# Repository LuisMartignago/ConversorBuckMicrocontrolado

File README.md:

# Conversor Buck Microcontrolado

Projeto de um conversor CC-CC abaixador (Buck Converter) com controle digital implementado em um microcontrolador **CH32V003**, desenvolvido com foco em aplicações de eletrônica de potência, sistemas embarcados e controle digital.

O projeto contempla o desenvolvimento completo do hardware e do firmware, incluindo o dimensionamento da etapa de potência, condicionamento dos sinais analógicos, controle por PWM, algoritmo de controle PI, proteção contra sobrecorrente e interface de comunicação serial.

---

## Principais características

* Conversor Buck microcontrolado.
* Controle digital de tensão utilizando controlador **PI**.
* Geração de PWM por hardware utilizando o temporizador **TIM1**.
* Aquisição de tensão e corrente através do ADC.
* Conversão automática utilizando **ADC + DMA**.
* Comunicação serial UART para monitoramento e configuração.
* Limitação de corrente por software.
* Controle de rampa (*Rate Limiter*) para partida suave e alterações da referência.
* Proteção contra *Integral Windup*.
* Firmware desenvolvido em linguagem C.
* Hardware desenvolvido no KiCad.

---

## Hardware

O conversor é composto pelos seguintes blocos principais:

* Microcontrolador **CH32V003**;
* Conversor Buck de potência;
* Driver para acionamento do MOSFET;
* Fonte auxiliar isolada para alimentação do gate driver;
* Reguladores de tensão para alimentação dos circuitos de controle;
* Divisor resistivo para medição da tensão;
* Resistor shunt para medição da corrente;
* Amplificador operacional interno do CH32V003 para condicionamento do sinal de corrente.

---

## Estratégia de controle

O controle da tensão de saída é realizado por um controlador **Proporcional–Integral (PI)**.

A implementação inclui:

* cálculo periódico do erro;
* atualização do termo integral;
* limitação do integrador (*Anti-Windup*);
* saturação da saída do controlador;
* atualização do ciclo de trabalho do PWM.

Para reduzir transitórios durante alterações da referência, foi implementado um algoritmo de **Rate Limiter**, permitindo variações graduais da tensão de saída.

Como mecanismo adicional de proteção, quando a corrente ultrapassa o limite configurado, a referência de tensão é reduzida gradualmente e o integrador do controlador é parcialmente descarregado, proporcionando recuperação rápida após a remoção da condição de sobrecorrente.

---

## Comunicação Serial

O firmware disponibiliza uma interface UART para:

* monitoramento da tensão;
* monitoramento da corrente;
* ajuste de parâmetros;
* depuração do sistema.

A transmissão utiliza **DMA**, reduzindo significativamente a utilização da CPU.

---

## Estrutura do repositório

```text
.
├── Firmware/
├── Hardware/
│   ├── Esquemáticos
│   ├── PCB
│   └── Bibliotecas
├── Documentação/
├── Imagens/
└── README.md
```

---

## Ferramentas utilizadas

* KiCad
* GCC para RISC-V
* WCH MounRiver Studio
* Git
* GitHub

---

## Aplicações

Este projeto pode ser utilizado como base para:

* estudos de Eletrônica de Potência;
* Sistemas Embarcados;
* Controle Digital;
* Fontes chaveadas;
* Conversores CC-CC;
* projetos acadêmicos;
* trabalhos de conclusão de curso.

---

## Licença

Este projeto está disponibilizado para fins acadêmicos e de pesquisa.

---

Caso este projeto seja utilizado em trabalhos acadêmicos, solicita-se a devida citação do repositório.

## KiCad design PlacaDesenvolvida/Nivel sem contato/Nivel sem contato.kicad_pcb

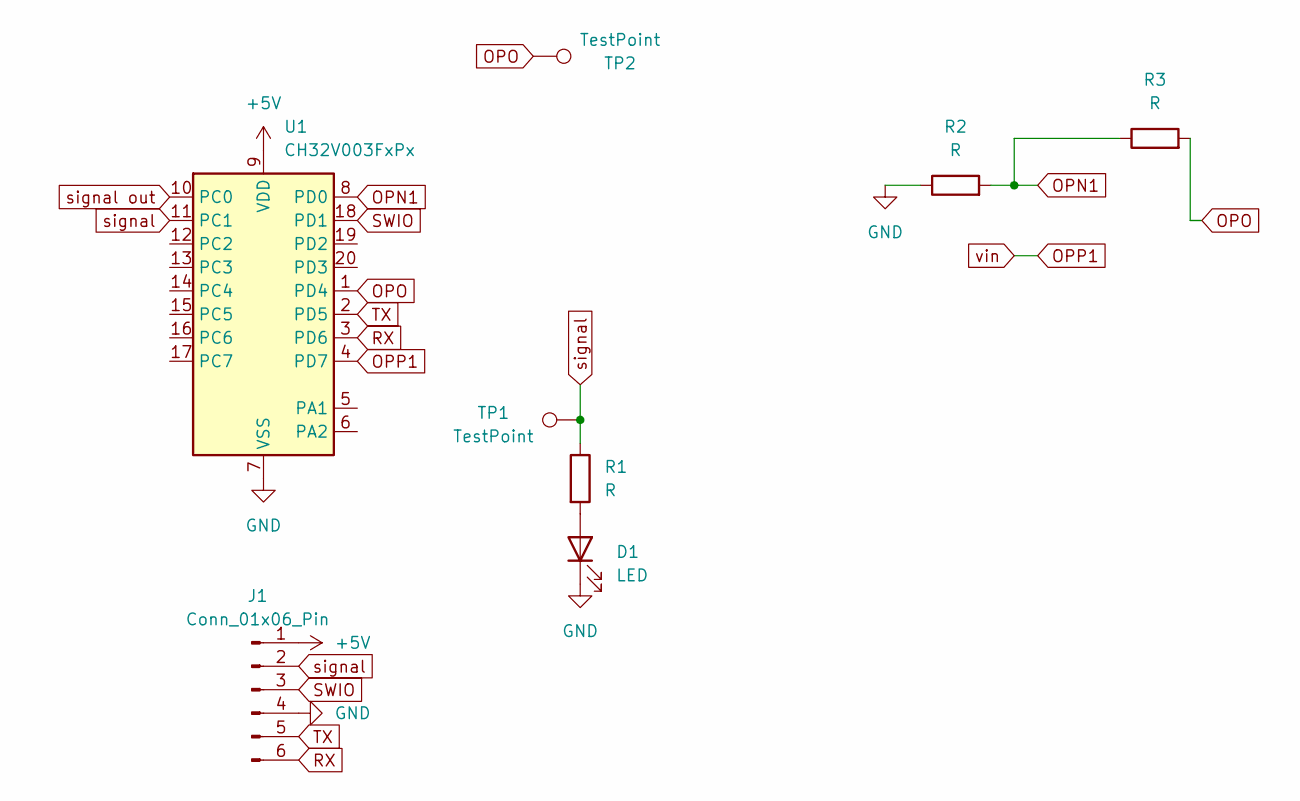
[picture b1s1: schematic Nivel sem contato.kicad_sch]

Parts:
D1: LED; LED_0805_2012Metric
J1: Conn_01x06_Pin; PinHeader_1x06_P2.54mm_Vertical
R1, R2, R3: R; R_0805_2012Metric
TP1, TP2: TestPoint; TestPoint_Bridge_Pitch2.54mm_Drill0.7mm
U1: CH32V003FxPx; TSSOP-20_4.4x6.5mm_P0.65mm

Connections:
+5V: J1.1, U1.9 (VDD)
GND: D1.1 (K), J1.4, R2.1, U1.7 (VSS)
unnamed: D1.2 (A), R1.2
OPN1: R2.2, R3.1, U1.8 (PD0)
OPO: R3.2, TP2.1 (1_1), U1.1 (PD4)
OPP1: U1.4 (PD7)
RX: J1.6, U1.3 (PD6)
SWIO: J1.3, U1.18 (PD1)
TX: J1.5, U1.2 (PD5)
signal: J1.2, R1.1, TP1.1 (1_1), U1.11 (PC1)
signal out: U1.10 (PC0)

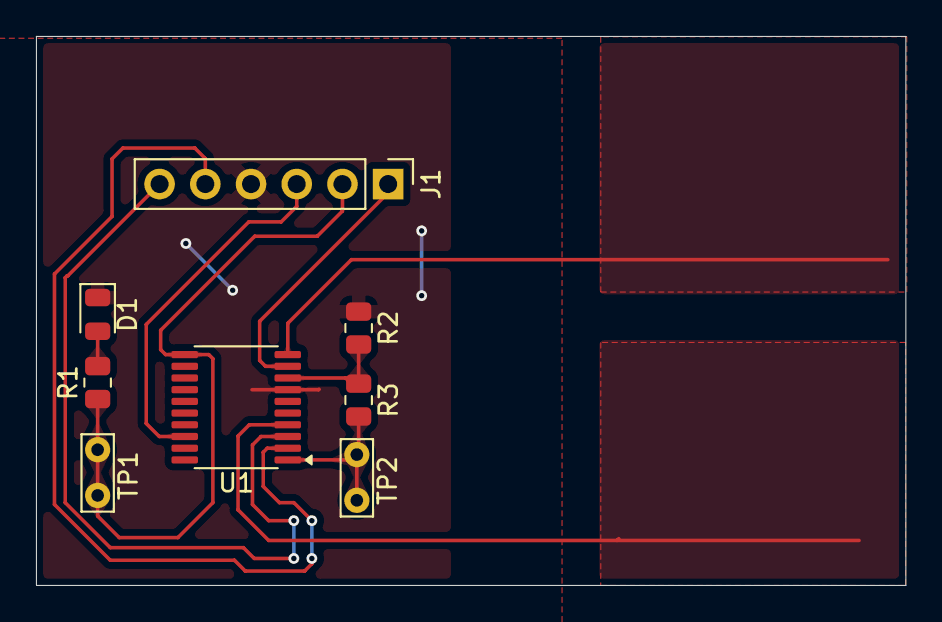
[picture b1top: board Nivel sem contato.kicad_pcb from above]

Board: 2 copper layers, 48.3 x 30.5 mm, 8 parts (0 on the bottom side), 9 nets.

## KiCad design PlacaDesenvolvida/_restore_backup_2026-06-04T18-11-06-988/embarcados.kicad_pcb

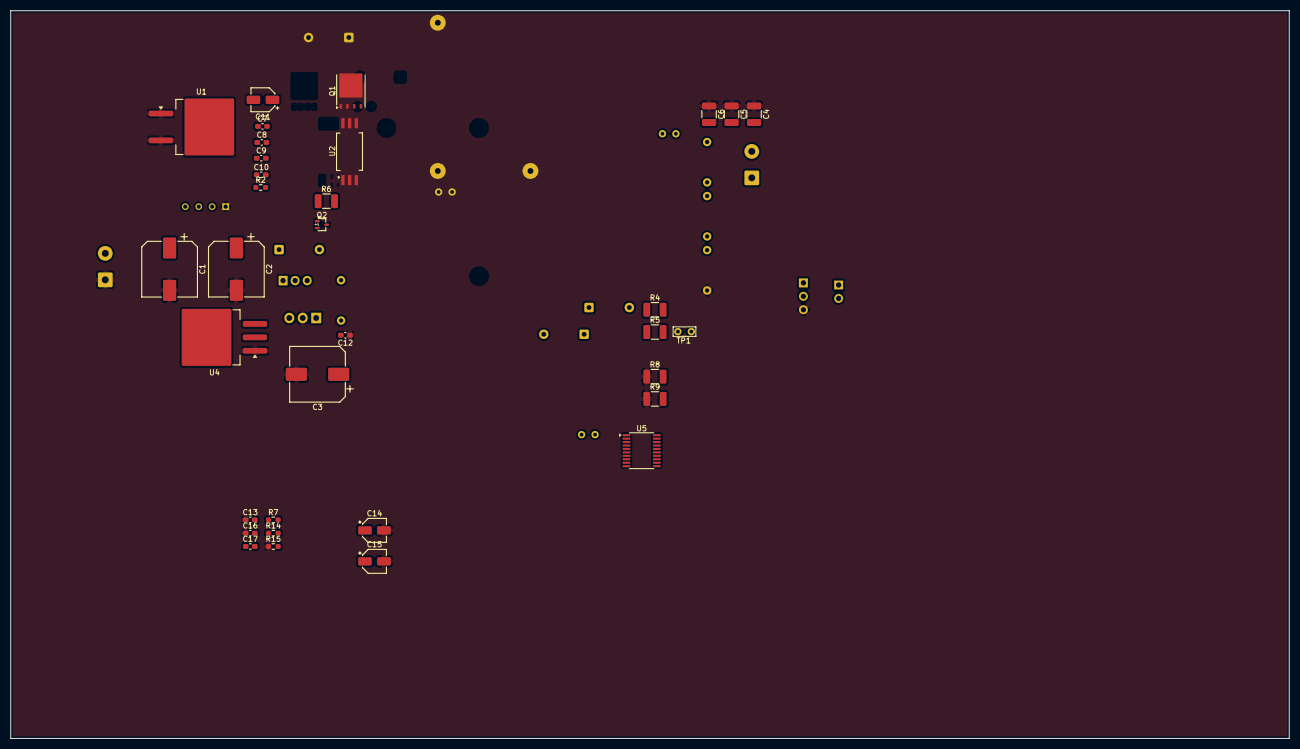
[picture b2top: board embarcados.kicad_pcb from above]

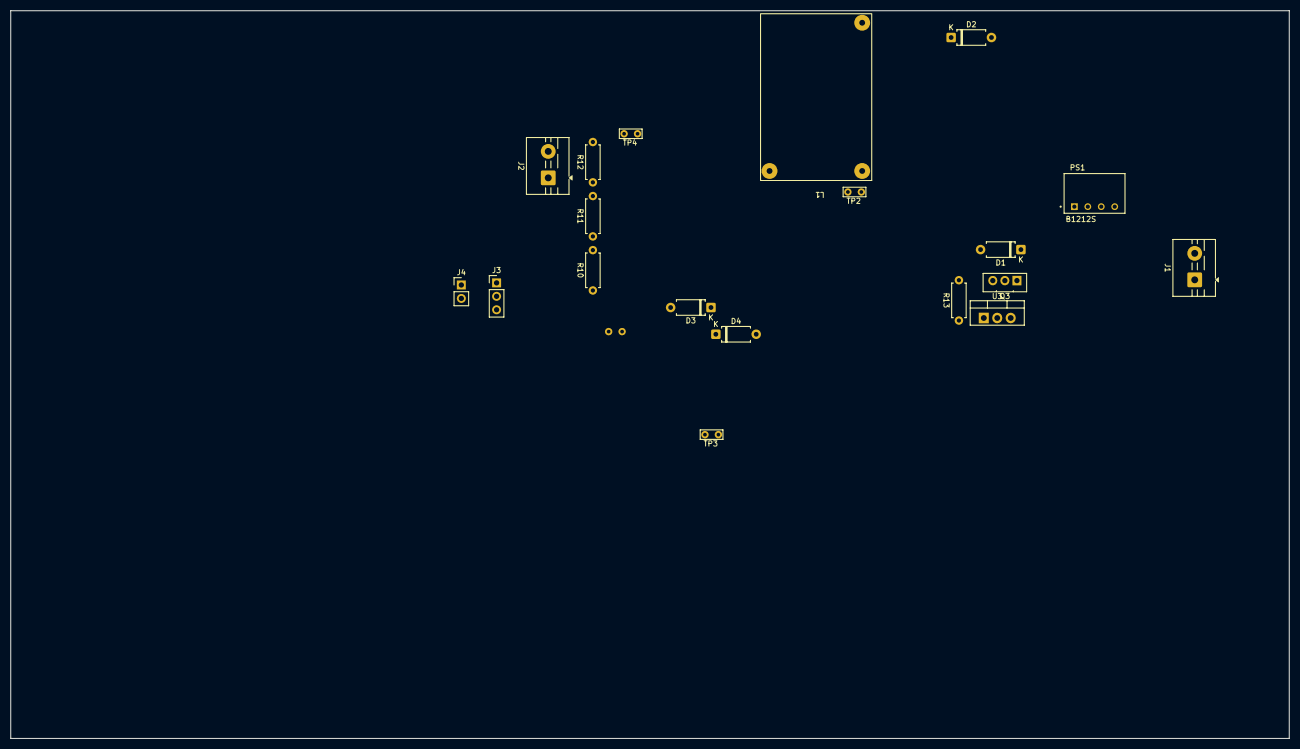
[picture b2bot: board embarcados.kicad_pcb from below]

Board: 2 copper layers, 241.5 x 137.5 mm, 52 parts (19 on the bottom side), 24 nets, no tracks yet.

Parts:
C1, C2, C3: 220uF; CP_Elec_10x10
C4, C5, C6: 10uF; C_1210_3225Metric_Pad1.33x2.70mm_HandSolder
C7, C8, C9, C10, C12, C13, C16: 0u1; C_0603_1608Metric_Pad1.08x0.95mm_HandSolder
C11, C14, C15: 10u; CP_Elec_4x3.9
C17: 12p; C_0603_1608Metric_Pad1.08x0.95mm_HandSolder
D1: D_Zener; D_A-405_P7.62mm_Horizontal
D2: ZMM15V; D_A-405_P7.62mm_Horizontal
D3, D4: 1N4148; D_A-405_P7.62mm_Horizontal
J1, J2: Screw_Terminal_01x02; TerminalBlock_MaiXu_MX126-5.0-02P_1x02_P5.00mm
J3: Conn_01x03_Pin; PinHeader_1x03_P2.54mm_Vertical
J4: Conn_01x03_Pin; PinHeader_1x02_P2.54mm_Vertical
L1: 470u; IndutorEmbarcados
PS1: B1212S; B1212s
Q1: BSC190N15NS3G(TOKMAS); TDSON-8-1
Q2: PNP; SOT-323_SC-70
Q3: BD139; TO-126-3_Vertical
R2: 10kΩ; R_0603_1608Metric_Pad0.98x0.95mm_HandSolder
R4, R5: 10Ω; R_1210_3225Metric_Pad1.30x2.65mm_HandSolder
R6: 220R; R_1210_3225Metric_Pad1.30x2.65mm_HandSolder
R7: 4k7; R_0603_1608Metric_Pad0.98x0.95mm_HandSolder
R8, R9: 0R1; R_1210_3225Metric_Pad1.30x2.65mm_HandSolder
R10, R13: 10k; R_Axial_DIN0207_L6.3mm_D2.5mm_P7.62mm_Horizontal
R11, R12: 20k; R_Axial_DIN0207_L6.3mm_D2.5mm_P7.62mm_Horizontal
R14: 15k; R_0603_1608Metric_Pad0.98x0.95mm_HandSolder
R15: 330R; R_0603_1608Metric_Pad0.98x0.95mm_HandSolder
TP1: GATE; TestPoint_Bridge_Pitch2.54mm_Drill0.7mm
TP2: SOURCE; TestPoint_Bridge_Pitch2.54mm_Drill0.7mm
TP3: I_amp; TestPoint_Bridge_Pitch2.54mm_Drill0.7mm
TP4: VOUT; TestPoint_Bridge_Pitch2.54mm_Drill0.7mm
U1: MUR1620CT; TO-263-2
U2: FOD8342TR2; SSO-6_6.8x4.6mm_P1.27mm_Clearance8mm
U3: LM7812_TO220; TO-220-3_Vertical
U4: LM1084-5.0; TO-263-3_TabPin2
U5: CH32V003FxPx; TSSOP-20_4.4x6.5mm_P0.65mm

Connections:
+5V: C15.1, C16.2, J3.1, Q2.3 (E), U4.2 (VO), U5.9 (VDD)
+12V: C13.2, C14.1, PS1.2 (+VIN), U3.3 (VO), U4.3 (VI)
+12Visolated: C7.2, C8.2, C9.2, C10.2, C11.1, PS1.4 (+VOUT), U2.6 (VDD)
+24V: C1.1, C2.1, D1.1 (K), J1.2, Q1.5 (D), Q3.2 (C)
GND: C1.2, C2.2, C3.2, C4.1, C5.1, C6.1, C12.1, C13.1, C14.2, C15.2, C16.1, J1.1, J3.3, PS1.1 (-VIN), R8.1, R9.1, R10.1, R15.1, U1.1 (A), U1.3 (A), U2.2 (NC), U2.3 (CATHODE), U3.2 (GND), U4.1 (GND), U5.7 (VSS)
I_sense: J2.1, R8.2, R9.2, U5.4 (PD7)
unnamed: D1.2 (A), Q3.3 (B), R13.2
unnamed: D2.1 (K), Q1.4 (G), R2.2, R4.2, R5.2, TP1.1 (1_1)
unnamed: D3.2 (A), D4.1 (C), U2.5 (VO)
unnamed: D3.1 (C), R4.1
unnamed: D4.2 (A), R5.1
unnamed: Q2.2 (B), R7.2
unnamed: Q2.1 (C), R6.1
unnamed: C3.1, C12.2, Q3.1 (E), R13.1, U3.1 (VI)
unnamed: R11.2, R12.1
unnamed: R6.2, U2.1 (ANODE)
unnamed: C17.2, R14.2, R15.2, U5.8 (PD0)
unnamed: C17.1, R14.1, TP3.1 (1_1), U5.1 (PD4)
PD1: J3.2, U5.18 (PD1)
RX: J4.2, U5.3 (PD6)
TX: J4.1, U5.2 (PD5)
VSS: C7.1, C8.1, C9.1, C10.1, C11.2, D2.2 (A), L1.1, PS1.3 (-VOUT), Q1.1 (S), Q1.2 (S), Q1.3 (S), R2.1, TP2.1 (1_1), U1.2 (C), U2.4 (VSS)
Vout+: C4.2, C5.2, C6.2, J2.2, L1.2, R12.2, TP4.1 (1_1)
Vsense: R10.2, R11.1, U5.19 (PD2)
